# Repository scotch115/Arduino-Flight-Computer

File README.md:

# Arduino Telemetry

Arduino-based IMU telemetry system for model rockets. 

Phase 1: Build a basic Arduino project to learn basics of handling sensor data and developing on an MCU

Phase 2: Design and build a custom flight computer using accessible components and write flight-capable software.

Phase 3: Design and build a ground-control system to communicate with flight computer, handle launch sequence and startup, transmit data to and from the flight computer to a laptop.

Phase 4: Design and assemble the rocket airframe, mount the flight computer and Rotation Control System (RCS but not that kind ;P ), and test avionics and telemetry.

Phase 5: Build and test chute ejection system and determine required powder charge level.

Phase 6: Launch! 🚀

# Phase I - Research
## Temp Sensor PCB Design
### MK I
The MK I PCB was unfortunately unsuccessful, as I used the EasyEDA autoroute feature to try to solve track placement issues, however it did not take into account the possiblity of shorting the circuits, and neither did I, so my Arduino Nano blew a capacitor. Thankfully I have more, but this board was immediately decommissioned.

### MK II
The MK II PCB was carefully redesigned to improve upon the Mk I's failures by utilizing better component placement, built-in grounding pads, and hand-drawn track placement.

## Update:
Custom PCB worked after a slight modification to the electrical grounding system. Further research concluded that a "common ground" pin would have been more efficient and effective, than multiple pins.

# Phase II - Development
## Flight Computer
This is the assembled Mk.1 version of the flight computer, equipped with a barometer and IMU for tracking altitude, temperature, orientation, and velocity.

> UPDATE (MK. II)
>
> The flight computer has been upgraded to use the Adafruit Feather M0 with LoRa Radio @900Mhz, and the onboard IMU has been upgraded to the MPU 6050 with 6 DOF (and gyroscope!).

### MK.III
After working through various software iterations, the prototype board was complete and functional, but rather messy and utilized more patch wires than I preffered. Using the skills I learned from the PCB design in Phase 1, I began designing a new flight computer PCB, with the intent of using the same core components from the prototype board, allowing an easy transition of functionality, and requiring litte to no software logic changes. The Blep flight computer was developed, and serves as a major improvement in terms of efficiency, durability, and technological advancement. Having learned from my mistakes with the Phase 1 power management, I introduced a single common ground via on the PCB, as well as an entire "ground plane" within the layers of the PCB to ensure that all of the routes on the front and back of the board share a truly **common** ground.

# Phase III - Ground Control
## Mk. I
The AirLift Wi-Fi Co-Processor on both the Adalogger and Metro are able to successfully communicate with the Node-Red server, to send sensor data over UDP for collection and assimilation. The Node-Red dashboard is configured to not only build graphs in real-time, but also saves the data as it is received to a JSON file. 

## Mk. II
When the flight computer software is complete, the ground control system will be updated. Now that the onboard telemtry has shifted to use 900Mhz radio, the communication with the rocket will also be updated to use radio, and the data received by the ground control computer will be sent to a new server for analysis and logging. The new data analysis server utilizes Serial Studio instead of node-red, which is significantly more robust and efficient when dealing with high-speed data input, and doesn't suffer from the read/write operations to graphs, but still provides a JSON file as output for post-launch analysis. The primary MCU for the ground control computer will be a Teensy 3.2, connected to a LoRa Featherwing using the Teensy-Feather adapter board. 

# Phase IV - Rocket Design and Construction 
> ~~Currently doing research and teaching myself rocket mechanics to design and build a stable, efficient rocket.~~  
> UPDATE (9/2022): The rocket airframe is being designed simultaneous with Phase II, and rudimentary schematics will be included in this repo for future use. Old PCB schematics have been scrubbed from the project, as they are no longer relevant or necessary, and have been replaced by the Blep flight computer PCB files. Airframe construction will likely begin in the order planned.

# Phase V - Chute Ejection System
> Development still in progress...

# Phase VI - Launch!
> Development still in progress...

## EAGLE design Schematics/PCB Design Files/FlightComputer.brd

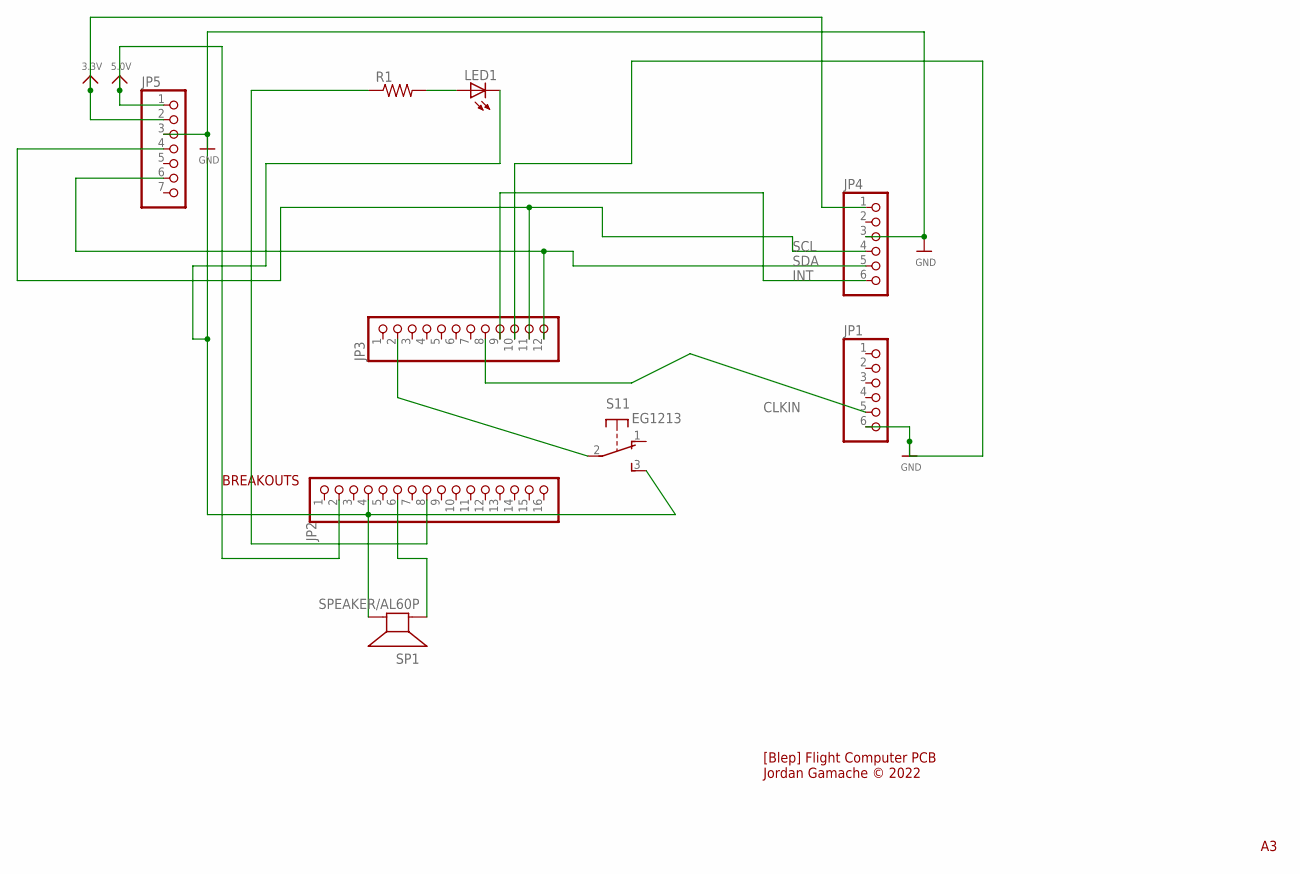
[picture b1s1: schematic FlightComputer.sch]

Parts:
JP1: HEADER-1X6ROUND; 1X06_ROUND
JP2: HEADER-1X16ROUND; 1X16_ROUND
JP3: HEADER-1X12; 1X12_ROUND
JP4: HEADER-1X670MIL; 1X06_ROUND_70
JP5: HEADER-1X770MIL; 1X07_ROUND_70
LED1: LED5MM
R1: R-US_0207/15; 0207/15
S1: EG1213
SP1: SPEAKER/AL60P; AL60P

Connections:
3.3V: JP4.1, JP5.2
5.0V: JP2.2, JP5.1
CLKIN: JP1.5, JP3.8
GND: JP1.6, JP2.4, JP3.10, JP4.3, JP5.3, LED1.K (C), S1.3 (S), SP1.2 (-)
INT: JP3.9, JP4.6
unnamed: JP2.6, SP1.1 (+)
unnamed: JP2.8, R1.1
unnamed: LED1.A, R1.2
unnamed: JP3.2, S1.2
SCL: JP3.11, JP4.4, JP5.4
SDA: JP3.12, JP4.5, JP5.6

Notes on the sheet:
BREAKOUTS
[Blep] Flight Computer PCB Jordan Gamache © 2022

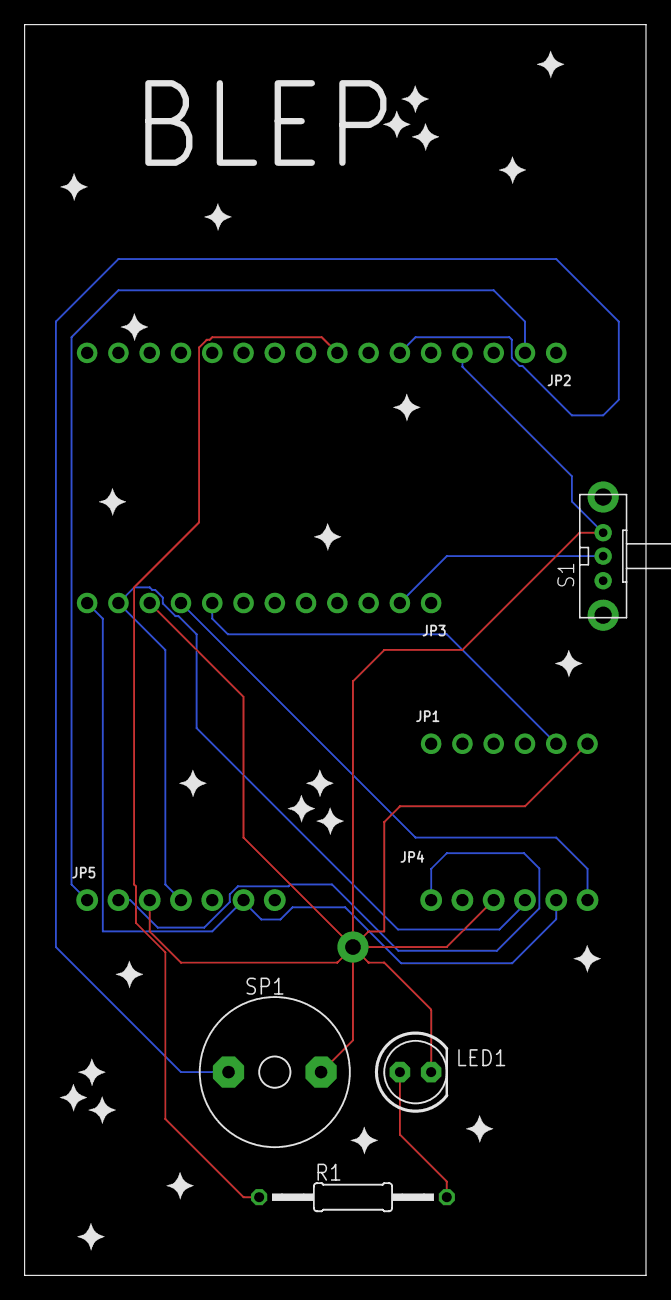
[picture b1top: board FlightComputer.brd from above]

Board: 2 copper layers, 50.5 x 101.6 mm, 9 parts (0 on the bottom side), 11 nets.

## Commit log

2020-09-25 Added accelerometer code
    Currently being run on (SparkFun) ProMicro
2020-09-25 Added visibility to serial console
2020-09-26 Added images and schematics for custom PCBs
2020-10-01 Developed node-red connection to nano, made programmatic changes for better graph readings.
2020-10-02 Fixed accelerometer code to output proper data and worked on output formatting on both boards.
2020-10-05 separated accelerometer and barometer files, and added WiFi support to barometer (main) file.
2020-10-10 Working on developing communications between flight computer and server.
2020-10-10 Fixed README output
2020-10-10 Established communication between Feather and Metro boards
2020-10-11 Assembled flight computer components on proto-board and added LED indicators
2020-10-11 Cleanup
2020-10-11 Added images and updated README
2020-10-11 Update README.md
    Fixed image loading error
2020-10-11 Final push
2020-10-11 Included node-red flow code
2020-10-11 Changed digitalWrite to analogWrite for LED power. Scrapped battery level code due to disk space limitations.
2021-10-25 Pushing current working code to repo
2021-10-25 Removed unnecessary wifi credentials
2021-10-25 Added tentative airframe schematics
2021-10-29 Updated Node-Red source file for telemetry monitoring
2021-10-31 Cleaned ground control code
2022-09-17 Updated test code, and fixed code structure. Prepping code for major update
2022-09-21 Created more robust serial output for better flight software testing and data logging.
2022-09-26 Improved IMU data collection, uploaded schematics and updated readme
2022-09-29 Added new PCB schematics
2022-10-04 Added missing commit from minor/v1.3 to master
2022-10-10 Added new flight computer image
2022-10-10 Updated Roadmap to reflect recent progress
2022-10-19 Created header files for simplicity and abstracted code for cleanliness
2022-10-25 Added new sync method to begin development of telementry link

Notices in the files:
parts and their libraries:
microbuilder: This work is placed in the public domain, and may be freely used for commercial and non-commercial work with the following conditions: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
